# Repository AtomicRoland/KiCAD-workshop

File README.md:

_KiCAD workshop_

These are the files that I used during the KiCAD workshop for the Big Ben Club (Dutch Acorn User Group) at the meeting on June 1st, 2024.
Feel free to use and improve this design as you like.

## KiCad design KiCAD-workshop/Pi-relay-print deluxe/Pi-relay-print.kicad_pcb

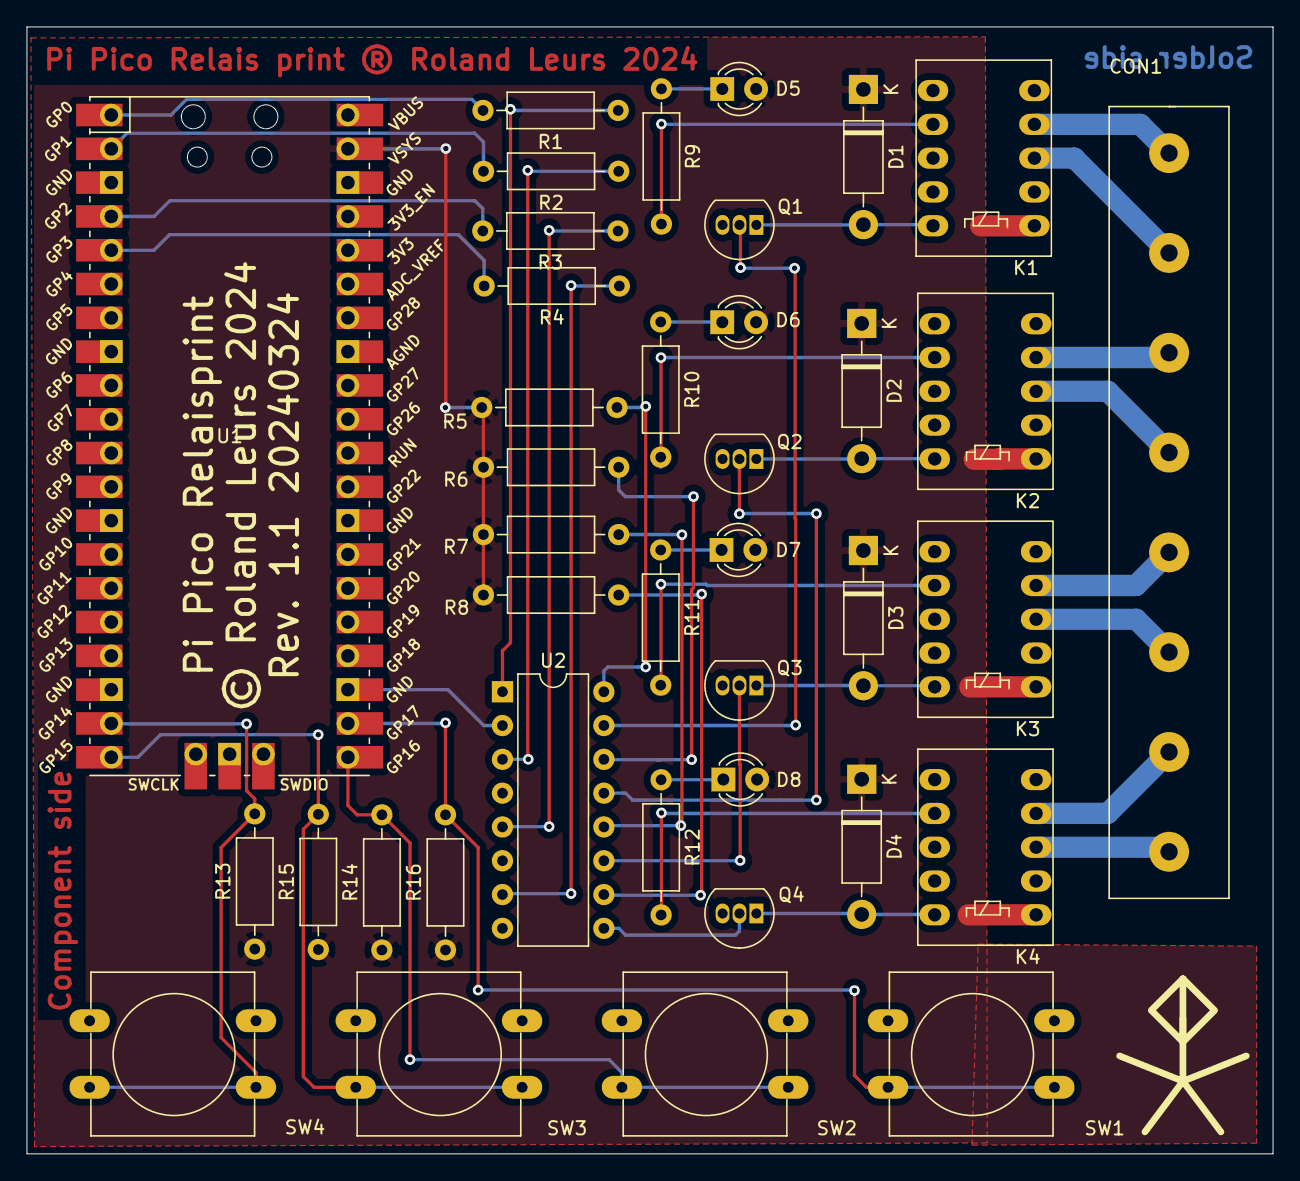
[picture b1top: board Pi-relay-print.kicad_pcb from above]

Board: 2 copper layers, 93.6 x 84.7 mm, 39 parts (0 on the bottom side), 42 nets.

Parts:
CON1: AKL171-08
D1, D2, D3, D4: 1N4007; D_DO-41_SOD81_P10.16mm_Horizontal
D5, D6, D7, D8: LED; LED_D3.0mm
K1, K2, K3, K4: AZ850-x; Relay_DPDT_FRT5
Q1, Q2, Q3, Q4: BC547; TO-92_Inline
R1, R2, R3, R4: 2k2; R_Axial_DIN0207_L6.3mm_D2.5mm_P10.16mm_Horizontal
R5, R6, R7, R8: 270Ω; R_Axial_DIN0207_L6.3mm_D2.5mm_P10.16mm_Horizontal
R9, R10, R11, R12: 4k7; R_Axial_DIN0207_L6.3mm_D2.5mm_P10.16mm_Horizontal
R13, R14, R15, R16: 10kΩ; R_Axial_DIN0207_L6.3mm_D2.5mm_P10.16mm_Horizontal
SW1, SW2, SW3, SW4: SW_Push; SW_PUSH-12mm
U1: Pico; RPi_Pico_SMD_TH
U2: LTV-844; DIP-16_W7.62mm

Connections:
GNDD: K1.8, K2.8, K3.8, K4.8, Q1.3, Q2.3, Q3.3, Q4.3, SW1.1, SW2.1, SW3.1, SW4.1, U1.3, U1.8, U1.13, U1.18, U1.23, U1.28, U1.33, U1.38, U2.2, U2.4, U2.6, U2.8
unnamed: CON1.1, K1.4
unnamed: CON1.2, K1.3
unnamed: CON1.3, K2.4
unnamed: CON1.4, K2.3
unnamed: CON1.5, K3.4
unnamed: CON1.6, K3.3
unnamed: CON1.7, K4.4
unnamed: CON1.8, K4.3
unnamed: D1.2, K1.10, Q1.1
unnamed: D2.2, K2.10, Q2.1
unnamed: D3.2, K3.10, Q3.1
unnamed: D4.2, K4.10, Q4.1
unnamed: D5.1, R9.1
unnamed: D6.1, R10.1
unnamed: D7.1, R11.1
unnamed: D8.1, R12.1
unnamed: K1.7, R9.2
unnamed: K2.7, R10.2
unnamed: K3.7, R11.2
unnamed: K4.7, R12.2
unnamed: Q1.2, U2.15
unnamed: Q2.2, U2.13
unnamed: Q3.2, U2.11
unnamed: Q4.2, U2.9
unnamed: R1.1, U2.1
unnamed: R1.2, U1.1
unnamed: R2.1, U2.3
unnamed: R2.2, U1.2
unnamed: R3.1, U2.5
unnamed: R3.2, U1.4
unnamed: R4.1, U2.7
unnamed: R4.2, U1.5
unnamed: R5.2, U2.16
unnamed: R6.2, U2.14
unnamed: R7.2, U2.12
unnamed: R8.2, U2.10
unnamed: R13.2, SW4.2, U1.19
unnamed: R14.2, SW2.2, U1.21
unnamed: R15.2, SW3.2, U1.20
unnamed: R16.2, SW1.2, U1.22
VCC: D1.1, D2.1, D3.1, D4.1, D5.2, D6.2, D7.2, D8.2, K1.1, K2.1, K3.1, K4.1, R5.1, R6.1, R7.1, R8.1, R13.1, R14.1, R15.1, R16.1, U1.39

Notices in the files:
KiCAD-workshop/Pi-relay-print deluxe/Pi-relay-print.kicad_pcb:
© Roland Leurs 2024
